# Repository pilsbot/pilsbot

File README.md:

# pilsbot 
Automate your pils transportation!

lscode: [O+S++I!CE-MV---!PSD-](https://lscodes.pke.fyi/api/decode?q=O+S++IE-MV---!PSD-)

This project intends to build an autonomous lorry for transporting pils-beer and other beverages, while following its "flock" - us humans.
It does so by using cheap hoverboard-hub-motors and entry-level robotics equipment (i.e. a jetson nano, OAK-D stereo camera).
The driving is solved simply by measuing the steering angle and odometry along with a mixture of differential drive and ackermann steering, resulting in a new driver - ackerdiff (see https://github.com/pilsbot/pils_control) and the interface to the hoverboard (see https://github.com/pilsbot/pilsbot_hw_ros).

For installation, see [here](https://github.com/pilsbot/pilsbot/wiki/Installation) or [here](https://github.com/pilsbot/pilsbot_vscode_ws).

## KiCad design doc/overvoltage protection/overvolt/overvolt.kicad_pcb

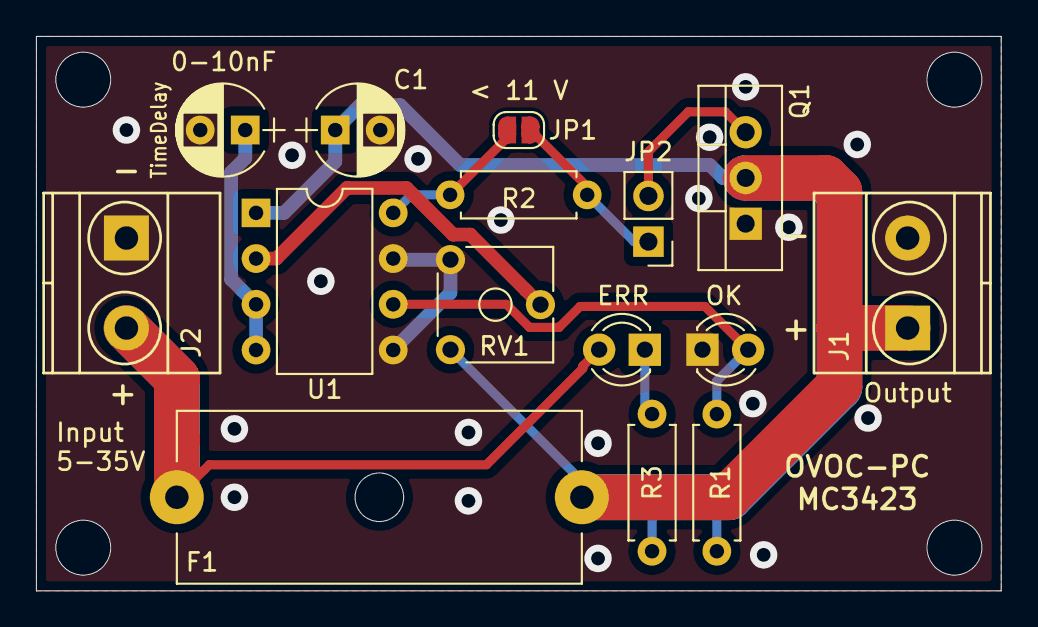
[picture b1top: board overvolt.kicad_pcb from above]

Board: 2 copper layers, 53.6 x 30.8 mm, 15 parts (0 on the bottom side), 10 nets.

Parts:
C1: 300µ; CP_Radial_D5.0mm_P2.50mm
D1: GRN LED; LED_D3.0mm
D2: RED LED; LED_D3.0mm
F1: Fuse; Fuseholder5x20_horiz_open_Schurter_0031_8201
J1: Output; TerminalBlock_Phoenix_MKDS1.5-2pol
J2: Input; TerminalBlock_Phoenix_MKDS1.5-2pol
JP1: < 11 V; SolderJumper-2_P1.3mm_Open_RoundedPad1.0x1.5mm
JP2: Jumper; Pin_Header_Straight_1x02_Pitch2.54mm
Q1: 2N6504D; TO-220-3_Vertical
R1: 1k; R_Axial_DIN0207_L6.3mm_D2.5mm_P7.62mm_Horizontal
R2: R; R_Axial_DIN0207_L6.3mm_D2.5mm_P7.62mm_Horizontal
R3: 3kR; R_Axial_DIN0207_L6.3mm_D2.5mm_P7.62mm_Horizontal
RV1: 2nd Half < 10k; Potentiometer_Trimmer_ACP_CA6v_Horizontal
TimeDelay: 0-10nF; CP_Radial_D5.0mm_P2.50mm
U1: MC3423; DIP-8_W7.62mm

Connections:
GND: C1.2, D1.1, J1.2, J2.1, Q1.1, RV1.3, TimeDelay.2, U1.5, U1.7
unnamed: C1.1, F1.2, J1.1, Q1.2, R1.1, R3.1, RV1.1, U1.1
unnamed: D1.2, R1.2, U1.6
unnamed: D2.1, R3.2
unnamed: JP1.1, R2.2, U1.8
unnamed: JP1.2, JP2.1, R2.1
unnamed: JP2.2, Q1.3
unnamed: RV1.2, U1.2
unnamed: TimeDelay.1, U1.3, U1.4
VCC: D2.2, F1.1, J2.2

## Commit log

2019-08-12 added first draft
2019-08-13 Mocked Sackermann, Addresses #2
2019-08-13 Added battery mockup
2019-08-14 Hackermann best ackermann
2019-08-15 I think, I overengineer this
2020-05-25 Bought Bollerwagen, so added axle-adapter for Hoverboard-motors
2020-05-26 reality
2020-05-27 Yo, first prototype works
2020-05-28 added some photos
2020-05-28 crop your shit
2020-05-29 better = better
2020-05-29 lol doof
2020-05-30 dummheit ist doof
2020-06-05 transfer repo
2020-06-05 Added first version of logo.
2020-06-05 fixed edges
2020-06-08 moving logo
2020-06-08 Added logo repo
2020-07-12 fIRXST VERSION OF wheel encoder
2020-07-13 Adapted some numbers #12
2020-07-13 Added rosserial node
2020-07-14 Communication possible for #13
2020-07-14 away!
2020-07-15 less holes for less falling down
2020-07-15 endstop switch holder
2020-07-15 reality!
2020-07-15 Allow for TAPPTPTPTAP!
2020-07-17 Batteryholder
2020-07-20 Hey mortyyyyyy Screw head is exactly as big as the hole was. Very tedious work getting the encoder on or off.
2020-07-21 Update .gitmodules
    Applied move
2020-07-28 Update?
2020-07-28 Added lighting repo
2020-07-28 Update Image
2020-07-28 Added submodule
2020-07-28 Moved Hole
2020-08-04 Removed non-fetchable microcontroller repo
2020-08-04 Removed hoverboard submodule for re-setup
2020-08-04 Re-added hoverboard repo, sanitizing commit history
2020-08-04 Updated submodule branch
2020-10-25 bump submodules
2020-10-25 Added slack in x and y potentiometer to reduce mechanical stresses
2020-10-26 More stability
2020-10-26 Two holed slip stop
2020-11-06 bump head_mcu
2020-11-11 Added donate button
2020-12-13 Lol lscode
2021-01-03 Scrobbled together little expanderboard for Solid State Relais and (maybe) future Pins that tolerate 25mA instead of 1mA.
2021-05-25 Added Documentation of newer EE
2021-05-31 Initial Overvolt-PCB design
2021-06-11 PCB in factory, lets see the first results
2021-06-11 Moved overvolt to own repo
2021-06-11 added forgotten 3d-Models
2021-11-16 added fixing
2021-11-16 stand to be printed
2021-11-16 Added one part of a new stand
2021-11-18 Less clearence
2021-12-26 Better (but still suboptimal) ficature for steering axle
2021-12-26 Added Voltage display. Man, freeCAD is not amused about changes in base geometry
2021-12-27 This FreeCAD really does not like changes, bruh
2021-12-28 Quick & dirty XT-60 female hodler
2021-12-28 More slack needed
2021-12-30 correctly sized holes
2021-12-30 More exact hole for supressing z-axis slip
2021-12-30 Added feet for mountplate to be fixed onto bollerwagen plate
2021-12-30 Didn't hit the hole exactly
2022-01-12 Added holder for the hoverboard button
2022-03-26 Added untested clamp model
2022-03-26 Increased clearance
2022-03-26 Eh, something about clearance and less slip for anti-turn hole
2022-03-27 Actual measurements
2022-03-27 Better clearance
2023-01-08 Fixes
2023-01-08 Added Raspi cam holder on aluprofil
2023-01-08 More clamping
2023-01-08 Forgot file
2023-01-17 Initial version of handle holder
2023-01-19 First version of OAK-D mount that doubles as (rain) protective cap for CSI-Cable
2023-01-21 Initial version of cable strain protector
2023-01-21 First steps for battery slide-in holder for big Battery
2023-01-21 Initial version of back side battery Holder cup
2023-01-21 A bit smaller
2023-01-21 Comply with screwas poking out
2023-01-21 Added Slit for piping cables
2023-01-21 Increased clearance to battery
2023-01-21 All the right holes in all the right places
2023-01-21 Added inital version of holder for splashwaterbox
2023-01-22 Da war ja was
2023-01-22 Added front holder. Even more clearance needed, TODO: Check if still fits
2023-01-28 Improved Clearance
2023-01-28 Thinner holder
2023-01-29 Initial version of Deckel
2023-01-29 Added Taper to allow for more water to just wash off. TODO: Is this contraproducti ve? Also, should a top shield for the camera objective be added?
2023-01-29 Updated some documetation images
2023-01-29 Initial version of HB-driver protection
2023-02-14 Initial version of Navsat-Receiver holder sock
2023-02-14 Fits roughly
2023-02-14 Initial Version of ssd holder
2023-06-11 Steering encoder capsule now stronger and less play. Todo: test
2023-06-13 Less pressure. Fits now.
2023-11-22 Initial version of indicator slots
2023-11-22 Made indicator slots directional
2023-12-04 Quick and dirty case for rp2040
2024-02-01 ups, lost the axis plug
2024-02-19 More space for zipties
2024-02-20 Increased wall strength a bit, considering that it was destroyed by a boßelball
2024-03-05 Do not lift here
2024-03-08 Zip-slots now more on the important places (außen)
2024-06-01 Made button holder somewhat sturdier
2024-06-01 Added new logging case
2024-06-01 Axis fastener to fasten now without destroying it
2024-06-01 Forgot adding exports
2024-08-05 Worked first try, lol
2025-06-03 Sturdy, but slightly less bulky indicators
2025-09-07 Indicator Slots now even more rugged, also GNSS and cam Holder fitting to the movable boom (Schubladenschiene)
2025-10-21 lighting-case to have a (native) screw hole
2025-10-21 Added tabs for rp2040 holder so that the deggel does not fall off that easily
2025-10-21 Hab nur ne kleinere schraube
2025-10-21 Noticed that more wiggle room would be nice
2025-10-21 Fixup: Unintentionally deleted a line
2025-12-13 Made manual override holder a little more sturdy
2025-12-14 Maybe fitting Antenna holder for better Bluetooth coverage
2025-12-14 Needed a little more sturdy cable mounts

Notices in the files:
doc/overvoltage protection/overvolt/overvolt.kicad_pcb:
(c) 2021 Pascal Pieper
